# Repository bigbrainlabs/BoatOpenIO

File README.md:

# BoatOpenIO

**Universal Marine IO System – Open Source, modular, fully configurable**

> *"Plug in, configure, done."*

BoatOpenIO is an open hardware platform for sensor integration on boats. Each of the 16 sensor terminals can be freely assigned to any of the up to 16 input channels via software. Pluggable mini-boards handle signal conditioning — no soldering, no rewiring.

Part of the **[Logbook Without Posing](https://www.amazon.com/s?k=logbook+without+posing)** series – Volume 3.

---

## 📚 Support the project

This project is 100% open source and free. The complete story – every idea, mistake, detour and solution – is documented in the book series **"Logbook Without Posing"**.

If you find this project useful and want to support it: buying the books is the best way.

> *"Found this useful? Grab a book — or the whole series. You'll be supporting further development."*

**[👉 Logbook Without Posing on Amazon](https://amzn.to/4e5swN6)**

> **Note:** The ready-made board set is no longer sold on Tindie. Due to the new EU regulation on shipping abroad, the effort is no longer proportionate for me as a private individual. The Gerber files in this repo remain free to download.
>
> **The boards can be purchased directly from PCBWay** — I've set them up there as projects, so there's nothing to upload yourself: **[👉 BoatOpenIO projects on PCBWay](https://www.pcbway.com/project/member/?bmbno=0EDF2E80-7ABD-44)**

### 🏭 Boards sponsored by PCBWay

**[PCBWay](https://www.pcbway.com)** sponsors the board manufacturing for BoatOpenIO, the sensor gateway of this ecosystem — thank you!

**[👉 Order the boards directly: PCBWay project page](https://www.pcbway.com/project/member/?bmbno=0EDF2E80-7ABD-44)**

---

## ⚠️ Safety Warning

**Always verify which mini-board is plugged into which channel before applying power.**

Connecting 12V directly to a pull-up channel (instead of through a voltage divider) will destroy the MUX, all ADS1115 and the ESP32 through I2C chain reaction.

The input board includes protection circuitry (3.3V) on all 16 signal inputs — but correct mini-board assignment is still essential.

---

## Concept

Commercial marine IO systems cost hundreds of euros and are closed black boxes.

BoatOpenIO costs a fraction of that — and anyone can adapt, extend, and improve it.

```
Sensor → Mini-Board → JST 3-Pin → PCB → Zener Protection → MUX → ADS1115 → ESP32 → MQTT → BoatOS
```

---

## Who Is This For?

**If your boat was built before 2000, this project was built for you.**

Boats from that era came with **analog VDO sensors** — oil pressure, oil temperature, coolant temperature, tank level, RPM. These sensors are robust, time-tested, and still doing their job perfectly. The problem: no modern system speaks their language.

NMEA 2000 gateways that bridge analog signals to modern boat networks exist — but they cost **300–500€**, are closed proprietary boxes, and give you zero insight or control over what happens inside.

**BoatOpenIO is an open analog marine gateway.**

Plug in your existing VDO sensors. Get clean MQTT output. Forward to Signal K or BoatOS. Done — without replacing a single sensor, without rewiring, without a black box.

```
VDO sensor → BoatOpenIO → MQTT → Signal K / BoatOS → modern dashboard
```

> **Built for boats built before 2000 that will sail for another 20 years — and deserve a modern dashboard without a full refit.**

---

## Hardware – v2 PCB

Four separate boards, connected via IDC ribbon cables: **input board**, **main board**, **ESP32 adapter board**, and **VCC distributor**. Gerber files ready to order in `hardware/v2/*/gerber/`.

> 🛒 **Ordering the boards:** All four boards are set up as projects on PCBWay and can be purchased there directly: **[PCBWay project page](https://www.pcbway.com/project/member/?bmbno=0EDF2E80-7ABD-44)** — or upload the Gerbers to a PCB fab of your choice. Bare PCBs, components per the parts list below.

```
Input Board ──20-pin ribbon──> Main Board <──16-pin ribbon── ESP32 Adapter Board
                                    │
                               3-pin JST
                                    │
                               VCC Board
```

### Main Board Components

| Component | Description | Socketed |
|-----------|-------------|----------|
| ESP32-DEVKITC-32D-F (38-pin) | Microcontroller, WiFi, I2C, MUX control – on its own adapter board | ✅ |
| CD74HC4067 Breakout | 16:1 analog multiplexer | ✅ |
| ADS1115 Breakout (1×) | 16-bit ADC | ✅ |
| MPU6050 Breakout (GY-521) | 6-DOF IMU, tilt/impact detection | ✅ |
| AMS1117-3.3 Breakout | 5V → 3.3V regulator | ✅ |

**Everything socketed** — no component soldered directly. Faulty ESP32? Swap the adapter board. Done.

The ESP32 sits on its own dedicated adapter board. The first adapter board is designed for the 38-pin ESP32 DevKitC-32D — swappable and ready for future ESP32 variants.

### Protection Circuit (Input Board)

Every one of the 16 signal inputs has a hardware protection circuit, directly on the input board:

```
Sensor → Screw terminal → R_Pack08 (resistor network) → SP0503BAHTG (Zener array, 3.3V) → MUX signal
```

2× Bourns 4116R-1-102LF (R_Pack08, DIL-16, isolated) + 6× SP0503BAHTG (SOT-143, 3 channels each).

> ⚠️ **Pull-up voltage is 3.3V** — the ADS1115 VDD is at 3.3V; higher voltages on the inputs risk component damage.

#### Running without the protection circuit (not recommended)

If the Bourns or Zener components are unavailable and you want to get the board running first, the resistor networks can be bypassed — but understand what you are giving up.

**How to bypass the Bourns 4116R-1-102LF:**  
The DIL-16 package contains 8 isolated resistors. Each resistor connects a pin on the left row to the opposing pin on the right row:

```
Pin 1  ──[R]──  Pin 16
Pin 2  ──[R]──  Pin 15
Pin 3  ──[R]──  Pin 14
  ...             ...
Pin 8  ──[R]──  Pin 9
```

To bypass: solder a short jumper wire across each pair (8 bridges per chip, 16 total for both R_Pack08). The signal then passes through without series resistance. The SP0503BAHTG Zener pads can simply be left empty.

> 🔴 **Without this protection, all 16 inputs are exposed.** A wrong mini-board, a wiring mistake, or any brief overvoltage can destroy the MUX, ADS1115, and ESP32 in a chain reaction — all three at once. Only bypass for bench tests with known, clean signals. Fit the real parts before installing on the boat.

### Input Board – Connectors

```
16× screw terminal 5.08mm   → raw sensor signal
20-pin IDC header            → connection to main board (SIG1–16 + GND)
```

### VCC Board – Connectors

The VCC board distributes power to the mini-boards via JST connectors. It connects to the main board via a 3-pin JST cable (5V, 3.3V, GND).

```
7× JST 2-pin (3.3V)         → VCC rail for passive/ESP01 mini-boards
3× JST 2-pin (5V)           → VCC rail for Arduino Nano mini-boards
3-pin JST                   → connection to main board (5V · 3.3V · GND)
```

### I2C Address

Only 1× ADS1115 fitted (the MUX routes all 16 channels onto a single signal line) → fixed address **0x48**.

### GPIO Assignment (ESP32, via 16-pin main board ↔ adapter board connector)

| GPIO | Function |
|------|----------|
| GPIO21 | I2C SDA |
| GPIO22 | I2C SCL |
| GPIO14 | MUX S0 |
| GPIO27 | MUX S1 |
| GPIO26 | MUX S2 |
| GPIO25 | MUX S3 |
| GPIO4 / 5 / 13 / 16 / 17 / 18 / 19 / 23 | OUT1–OUT8 (prepared for output channels) |

### Output Channels (prepared)

The main board already has a 10-pin header prepared for 8 signal output channels (+5V/GND) — e.g. for heaters, pumps, horns via relay or MOSFET mini-boards. Works on the same plug-in principle as the inputs.

### Compatible ESP32 Modules (first adapter board)

The footprint fits all modules in the 38-pin DevKitC layout: **ESP32-WROOM-32 / -32D / -32E / -32U / -32UE**, as well as **ESP32-SOLO-1**.

> ⚠️ **ESP32-WROVER is NOT compatible** — GPIO16/17 are internally reserved for PSRAM on WROVER and therefore blocked for output channels.

---

## Mini-Boards (pluggable)

| Type | Code | Use case |
|------|------|----------|
| Voltage divider | VT | 12V VDO sensors → 3.3V |
| Pull-down | PD | Digital sensors, switches |
| Pull-up | PU | Open-collector outputs |
| Schmitt trigger | ST | Magnetic pickup sensors, 50Hz generators |
| Pulse board | ISP | RPM, flow (Arduino Nano / ESP01) |
| Optocoupler | OPT | Galvanic isolation (W-terminal RPM) |
| Direct / jumper | DIR | 3.3V signals directly |
| GND collector | GND | Multiple sensor ground loops → single reference |

### MotorCombo — everything on one board

The **MotorCombo** taps the most common engine sensors directly, so you don't have to plug in six separate mini-boards:

| Channel | Conditioning |
|---------|--------------|
| Battery 1 + 2 | Voltage divider |
| Oil pressure | Pull-up |
| Temperature | Pull-up |
| Tank | Pull-up |
| RPM | Optocoupler + ESP-01 |

**[MotorCombo THT](hardware/mini-boards/MotorCombo_THT/README.md)** — through-hole, hand-solderable. Gerbers and documentation are in the repo. Resistor values are deliberately left open so everyone can fit what matches their own VDO senders — which is also why there is no pre-assembled SMD variant: with the values depending on the senders, a fixed pre-populated board makes no sense.

**Design and submit your own mini-boards** — pull requests welcome!

---

## Multiplexer Logic

The CD74HC4067 routes one of 16 inputs onto the shared ADS pin A0 via a 4-bit address (S3–S0). Address and chip input follow the datasheet: `0000 → C0` … `1111 → C15`.

> **Rev.1 note — channels are mirrored in software.** On the Rev.1 board the channel wiring is reversed (terminal 1 sits on the input that address `1111` selects, terminal 16 on `0000`). The firmware compensates in software (`MUX_MIRROR`): terminal *N* → address `16 − N`. The terminal numbering you see is therefore correct. A later board revision straightens the wiring, then the mirror is switched off (`MUX_MIRROR 0`).

| Terminal | Address S3 S2 S1 S0 | CD74HC4067 input |
|----------|---------------------|------------------|
| 1        | `1111`              | C15              |
| 2        | `1110`              | C14              |
| …        | …                   | …                |
| 16       | `0000`              | C0               |

---

## Software Configuration

```json
{
  "kanaele": [
    {"klemme": 1, "sensor": "battery1",     "einheit": "V",   "faktor": 4.7, "offset": 0, "aktiv": true,  "topic": ""},
    {"klemme": 2, "sensor": "oil_temp",     "einheit": "°C",  "faktor": 1.0, "offset": 0, "aktiv": true,  "topic": "vessels/self/propulsion/engine/oilTemperature"},
    {"klemme": 3, "sensor": "oil_pressure", "einheit": "bar", "faktor": 1.0, "offset": 0, "aktiv": true,  "topic": "vessels/self/propulsion/engine/oilPressure"},
    {"klemme": 4, "sensor": "tank",         "einheit": "%",   "faktor": 1.0, "offset": 0, "aktiv": true,  "topic": ""},
    {"klemme": 5, "sensor": "rpm",          "einheit": "rpm", "faktor": 1.0, "offset": 0, "aktiv": false, "topic": ""}
  ]
}
```

> All 16 channels are routed via the MUX (CD74HC4067) to a single ADS1115 @ 0x48 on pin A0. No `ads` or `pin` fields needed — the channel number (`klemme`) maps directly to the MUX select lines.
>
> **`topic`** — optional. If empty (`""`), the firmware publishes to `boat/io/<sensor>` (default). Set a custom topic for Signal K compatibility or any other MQTT schema. The "SK" button in the web UI auto-fills the correct Signal K path for common sensor names.

---

## MQTT Topics

```
boat/io/battery1          → 12.43
boat/io/oil_temp          → 87
boat/io/oil_pressure      → 3.2
boat/io/tank              → 48
boat/io/rpm               → 1450
boat/io/pitch             → 1.2        (configurable)
boat/io/roll              → -0.5       (configurable)
boat/alarm/impact_g       → 2.40       (impact base configurable)
boat/alarm/impact_severity → KRITISCH  (LEICHT / MITTEL / STARK / KRITISCH)
boat/alarm/impact_active  → true
boatopenio/status         → online
```

> **Channel topics** are set per channel (`topic` field / web UI). **Pitch, roll and the impact base topic** are editable under **WiFi & MQTT** in the web UI (defaults `boat/io/pitch`, `boat/io/roll`, `boat/alarm/impact`; the impact base gets `_g` / `_severity` / `_active` appended). In test mode the impact alarms are redirected to `boat/test/alarm/impact_*` so demo impacts never trigger real dashboards.

---

## Firmware Features

| Feature | Description |
|---------|-------------|
| Web UI | Configuration at `192.168.4.1`, bilingual DE/EN |
| WiFiManager | AP on first start for WiFi setup |
| MQTT | Publish all sensor values, LWT, auth support |
| OTA | Over-the-air firmware updates |
| mDNS | Reachable as `boatopenio.local` |
| Impact Detection | MPU6050 G-force monitoring with severity levels |
| Watchdog | Automatic restart on firmware hang |
| LittleFS | Persistent configuration storage |

---

## Supported Sensors

| Sensor | Type | Mini-Board |
|--------|------|------------|
| VDO temperature (NTC) | Resistance | VT |
| VDO oil pressure | Linear resistance | VT |
| VDO tank sender | Potentiometer | VT |
| Battery voltage 12V | Voltage divider | VT (10k/2.2k) |
| RPM (W-terminal) | Pulse/AC | OPT + ISP |
| RPM (magnetic pickup) | AC signal | ST + ISP |
| Fuel flow | Pulse | ISP |
| Bilge sensor | Digital | PD |
| Door/hatch contact | Digital | PD |
| DS18B20 temperature | Digital 1-Wire | custom board |

---

## Bill of Materials – PCB Kit

**[👉 Complete parts list on Amazon](https://www.amazon.de/hz/wishlist/ls/2ZLKK0GZJ5RZE?&linkCode=ll2&tag=bigbrainlab08-21&linkId=caccb90fad5cfe3e58063e29c1bc7dd4&ref_=as_li_ss_tl)**

> **Note:** Items 7, 8, 13, and 14 are from the same set — one purchase covers all. Same applies to 12 and 15.

| # | Component | Notes | Source |  |
|---|-----------|-------|--------|---|
| 1 | ESP32 DevKitC-32D (38-pin) | Main controller | [Amazon](https://amzn.to/441f1bl) |  |
| 2 | CD74HC4067 Breakout | 16:1 MUX | [Amazon](https://amzn.to/4vPmaHH) |  |
| 3 | ADS1115 Breakout (1×) | 16-bit ADC | [Amazon](https://amzn.to/4gg8mRQ) |  |
| 4 | MPU6050 Breakout (GY-521) | IMU | [Amazon](https://amzn.to/3S3gGKJ) |  |
| 5 | AMS1117-3.3 Breakout | Voltage regulator | [Amazon](https://amzn.to/4gfqqeL) |  |
| 6 | Female header assortment | Sockets for all breakouts | [Amazon](https://amzn.to/3S1rXLD) |  |
| 7 | Pin header 2×10 (20-pin) | Main board ↔ input board | [Amazon](https://amzn.to/4f2awU6) |  |
| 8 | Pin header 2×08 (16-pin) | Main board ↔ ESP32 adapter board | [Amazon](https://amzn.to/4f2awU6) |  |
| 9 | Screw terminals 5.08mm | 16× sensor inputs | [Amazon](https://amzn.to/4e6bJcN) |  |
| 10 | Bourns 4116R-1-102LF (2×) | Resistor network DIL-16 | [Conrad](https://www.conrad.de/de/p/bourns-4116r-1-102lf-4116r-1-102lf-widerstandsnetzwerk-1-k-radial-bedrahtet-dip-16-0-25-w-1-st-1055156.html) | [Amazon](https://amzn.to/3SuSZeD) |
| 11 | SP0503BAHTG (6×) | Zener array SOT-143 | [Amazon](https://amzn.to/4aippiv) |  |
| 12 | JST 2-pin connector | VCC rails | [Amazon](https://amzn.to/43y2Suh) |  |
| 13 | Pin header 2×10 (20-pin) | Input board side | [Amazon](https://amzn.to/4f2awU6) |  |
| 14 | Pin header 2×08 (16-pin) | ESP32 adapter board side | [Amazon](https://amzn.to/4f2awU6) |  |
| 15 | JST 2-pin connector (10×) | VCC distribution | [Amazon](https://amzn.to/43y2Suh) |  |
| 16 | Ribbon cable + IDC 20-pin | Main board ↔ input board | [Amazon](https://amzn.to/4w6858M) |  |
| 17 | Ribbon cable + IDC 16-pin | Main board ↔ ESP32 adapter board | [Amazon](https://amzn.to/3SuZ3DQ) |  |
| 18 | Pin socket 2×05 (10-pin) | SIG-OUT prep on main board | — |  |
| 19 | JST 3-pin connector | VCC board ↔ main board | [Amazon](https://amzn.to/4ush82N) |  |
| 20 | PCB set (4 boards) | Order the Gerbers in `hardware/v2/` yourself | [PCBWay](https://www.pcbway.com/project/member/?bmbno=0EDF2E80-7ABD-44) |  |

> Amazon: faster delivery. AliExpress links to follow.
>
> **Item 10 comes from Conrad**, not Amazon: the same Bourns part is around €1.30 there versus roughly €10. For the 2 pieces needed that saves nearly €18. The Amazon link beside it is just the fallback source.
>
> Item 20 is the bare boards only. Items 1–19 are the components you still need.

---

## Directory Structure

```
BoatOpenIO/
├── README.md                          ← English (this file)
├── README_de.md                       ← German version
├── LICENSE                            ← GPL-3.0
├── boatopenio_final_architektur.svg   ← system architecture diagram
├── firmware_src/
│   ├── firmware_src.ino               ← main firmware
│   ├── webui.h                        ← web UI & captive portal
│   └── data/
│       └── config.json                ← default channel config
├── hardware/
│   ├── boatopenio-gehaeuse-draufsicht.svg  ← housing top-view
│   ├── mini-boards/                   ← mini-board designs
│   └── v2/                            ← KiCad PCB project (4 boards)
│       ├── main-board/
│       │   └── gerber/main-board.zip
│       ├── input-board/
│       │   └── gerber/input-board.zip
│       ├── esp32-adapter-board/
│       │   └── gerber/esp32-adapter-board.zip
│       └── vcc-board/
│           └── gerber/vcc-board.zip
├── images/                            ← build photos
└── docs/
    ├── setup.md              / setup_de.md          ← commissioning guide
    ├── configuration.md      / configuration_de.md  ← config reference
    └── backend.md            / backend_de.md        ← firmware & backend reference
```

---

## Roadmap

What's done, what's planned, what's on the backlog — see [ROADMAP.md](ROADMAP.md).

---

## Integration with BoatOS

BoatOpenIO sends all values via MQTT. BoatOS auto-discovers all topics and displays them in the dashboard. No manual configuration needed.

**➡️ [github.com/bigbrainlabs/BoatOS](https://github.com/bigbrainlabs/BoatOS)**

---

## License

**GNU General Public License v3.0 (GPL-3.0)**

Free to use, modify, distribute — derivative works must also be GPL-3.0. See [LICENSE](LICENSE).

**Exception:** the community enclosure designs in `hardware/enclosures/` are licensed **CC BY-SA 4.0** — the better fit for CAD work. Submitting a design means licensing it that way; see the [enclosure README](hardware/enclosures/README.md).

---

## Part of the Series

**Logbook Without Posing** — authentic DIY projects around boating.

> *"Build it yourself and you know what's in it — and what it cost."*

📖 [Book series on Amazon](https://amzn.to/4e5swN6) · 🔧 [BoatOS](https://github.com/bigbrainlabs/BoatOS) · ⚡ [BoatOpenIO](https://github.com/bigbrainlabs/BoatOpenIO)

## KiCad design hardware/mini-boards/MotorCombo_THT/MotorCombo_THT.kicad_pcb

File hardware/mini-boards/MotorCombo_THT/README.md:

# MotorCombo THT — Combo Mini-Board for Engine Sensors

> 🚧 **Prototype stage.** This board (Rev.1) has not been fully validated yet. Five of the six channels are tested, the RPM channel is not (see below). Resistor values, mounting holes and layout may still change in future revisions. Build at your own risk, and ideally with feedback.

Through-hole (THT) variant of the MotorCombo board. Combines the six typical engine room signals onto a single board instead of plugging in six separate mini-boards.

Every part is through-hole — hand-solderable, no SMD equipment needed.

---

## Channels

| Channel | Connector | Signal conditioning | Typical sensor |
|---------|-----------|---------------------|----------------|
| Battery 1 | `Batt1` | Voltage divider (R1 / R2) | 12 V house voltage |
| Battery 2 | `Batt2` | Voltage divider (R3 / R4) | Second battery bank |
| Tank | `Tank1` | Pull-up to 3.3 V (R5) | VDO tank sender, resistive |
| Temperature | `Temp1` | Pull-up to 3.3 V (R6) | VDO temperature sender, resistive |
| Oil pressure | `Oil1` | Pull-up to 3.3 V (R7) | VDO pressure sender, resistive |
| RPM | `RPM1` | Optocoupler PC817 + ESP-01 | Alternator W terminal, pulse pickup |

Every channel has a 100 nF capacitor for signal smoothing (C1–C6).

> Channels 1–5 (`Batt1`, `Batt2`, `Tank1`, `Temp1`, `Oil1`) are **not hardwired** to one mode — two solder jumpers per channel select pull-up or voltage-divider. See [Channel Mode — Jumpers](#channel-mode--jumpers-channels-15). The table shows the typical default for each sensor.

---

## Signal Path

Per the netlist, the JST 3-pin connectors are wired as **input / GND / output**: the raw signal arrives on pin 1, the conditioned signal returns on pin 3.

```
Pin 1 (raw) → conditioning → Pin 3 (conditioned)
Pin 2 = GND
```

**Voltage divider (Batt1, Batt2)**
```
Pin 1 ──[R1]──┬── Pin 3
              ├── C1 ── GND
              └──[R2]── GND
```

**Pull-up (tank, temperature, oil)**
```
3.3 V ──[R5]──┬── Pin 1 = Pin 3
              └── C3 ── GND
```
Pin 1 and pin 3 are tied together — the resistive sender forms the divider together with the pull-up resistor.

**RPM (RPM1)**
```
Pin 1 ──[R8]── PC817 LED ── GND
               PC817 transistor ── GPIO0 (ESP-01), pull-up R9
               GPIO2 ──[R10]──┬── Pin 3
                              └── C6 ── GND
```
The optocoupler isolates the pulse input galvanically. The ESP-01 counts the pulses and outputs an RPM-proportional value on pin 3.

---

## Channel Mode — Jumpers (channels 1–5)

Channels 1–5 (`Batt1`, `Batt2`, `Tank1`, `Temp1`, `Oil1`) are **not hardwired to one mode**. Two solder jumpers **JP1** and **JP2** plus the channel's divider resistor **R2** select **pull-up** (resistive VDO senders) or **voltage-divider** (active voltage inputs) — per channel.

**JP1 (3 pads):**
- **P1 = 3.3 V** (pull-up)
- **P3 = SIG-IN** (voltage divider)
- **P2 = common** (centre pad)

| | Pull-up mode | Voltage-divider mode |
|---|---|---|
| **JP1** | bridge **P2–P3** | bridge **P2–P1** |
| **JP2** | **bridged** | **open** |
| **R2** (channel divider resistor) | **fit a bridge** (0 Ω) | **fit** |

- **Pull-up:** JP1 P2–P3 closed, JP2 closed, R2 position populated with a **bridge** (a 0 Ω resistor in the same footprint, or a wire link) — the pull-up is active and SIG-OUT is passed through. **Important:** do not leave R2 open here. The board has no separate direct GND connection, so the R2 position provides the ground for the smoothing capacitor; left open, the ceramic cap would sit in series in the signal path instead of to ground.
- **Voltage divider:** JP1 P2–P1 closed, JP2 open, R2 fitted — the divider is formed.

Channel 6 (`RPM1`) is the optocoupler + ESP-01 path and has no mode jumper.

---

## Connectors

| Designator | Type | Function |
|------------|------|----------|
| `Batt1`, `Batt2`, `Tank1`, `Temp1`, `Oil1`, `RPM1` | JST PH 3-pin, 2.0 mm | Channels to the main board |
| `J7` | JST PH 2-pin, 2.0 mm | 3.3 V / GND supply from the VCC board |
| `GND_Collector1` | Screw terminal 5-way, 5.08 mm | Common point for sensor grounds |

---

## Board

| | |
|---|---|
| Revision | Rev.1 |
| Dimensions | 75 × 55 mm |
| Layers | 2 |
| Assembly | through-hole throughout |
| Mounting | 4 holes, one per corner |
| Gerbers | [`gerber/`](gerber/) — ready to order, ZIP included |

> 🏭 **Order ready-made:** the boards are sponsored by [PCBWay](https://www.pcbway.com) and shared in the [PCBWay project](https://www.pcbway.com/project/member/?bmbno=0EDF2E80-7ABD-44) — order directly, no Gerber upload needed.
>
> 

---

## Bill of Materials

| Item | Part | Qty | Package |
|------|------|-----|---------|
| 1 | Resistor, axial | 10 | DIN0204, 7.62 mm pitch |
| 2 | Capacitor 100 nF, ceramic | 6 | disc D5 mm, 5.00 mm pitch |
| 3 | PC817 optocoupler | 1 | DIP-4 |
| 4 | ESP-01 (ESP8266) | 1 | ESP-01 module, 2×4 socket |
| 5 | JST PH header 3-pin, vertical | 6 | B3B-PH-K |
| 6 | JST PH header 2-pin, vertical | 1 | B2B-PH-K |
| 7 | Screw terminal 5-way | 1 | Phoenix MKDS-3/5-5.08 |

---

## Resistor Values

**Values R1–R10 are deliberately left open in the schematic.** VDO senders differ in resistance range depending on year and manufacturer — a value that works cleanly on one engine can cause distorted readings on the next. Rather than prescribing one size, everyone fits what matches their own senders.

The following values have proven themselves in practice and are a good starting point:

| Channel | Resistors | Recommended | Alternative |
|---------|-----------|-------------|-------------|
| Battery 1 | R1 / R2 | 10 kΩ / 2.2 kΩ | 100 kΩ / 22 kΩ |
| Battery 2 | R3 / R4 | 10 kΩ / 2.2 kΩ | 100 kΩ / 22 kΩ |
| Tank | R5 | 10 kΩ | adjust to your sender |
| Temperature | R6 | 10 kΩ | adjust to your sender |
| Oil pressure | R7 | 10 kΩ | adjust to your sender |

**Voltage dividers.** 10 kΩ / 2.2 kΩ is tested and works. The divider ratio is 2.2 / (10 + 2.2) = 0.180, so 12 V becomes roughly 2.16 V. As a factor in the channel configuration that works out to about **5.55**, and with a 3.3 V input limit the upper end lands at roughly 18 V. The 100 kΩ / 22 kΩ variant has the same ratio but loads the battery ten times less — at the cost of being more susceptible to interference.

**Pull-ups.** 10 kΩ has shown itself to be a good compromise in testing. If a sender uses a different resistance range, the pull-up should be adjusted along with it — best measured on the installed sender, choosing a value that makes good use of the measuring range.

**Optocoupler.** R8 sets the PC817 LED current, R9 is the pull-up at the ESP-01. This combination has not yet been proven in practice (see below).

---

## ESP-01 Notes

The ESP-01 is **socketed** — it needs a dedicated USB adapter for flashing anyway, so it is taken out of the board for programming. That is why `RST`, `URXD` and `UTXD` are left unconnected.

> 🚧 **The RPM channel via PC817 and ESP-01 has not been tested in practice yet.** The other five channels are proven.

Worth keeping in mind during assembly: on the ESP8266, `GPIO0` and `GPIO2` double as boot-mode straps, and both are wired here.

- **GPIO0** is tied to the optocoupler transistor. If a pulse happens to be present at power-on, the optocoupler pulls GPIO0 low and the ESP-01 boots into flash mode instead of running the firmware — quite possible with the engine running.
- **GPIO2** drives the output through R10. C6 is discharged at power-on — depending on the values chosen for R10 and C6, this may hold GPIO2 low for too long during boot.

Both depend on the values of R8, R9, R10 and C6, and can be settled together when the RPM channel is trialled.

> 💡 **Tip: use an ESP-01S instead of an ESP-01.** The newer ESP-01S variant already has a pull-up fitted on GPIO0. This mitigates the boot-mode issue above, since GPIO0 is safely held high at idle. The ESP-01S is pin-compatible and fits the same socket.

---

## Safety

> ⚠️ **Verify which channel sits on which terminal before applying power.**
>
> The battery channels are designed for 12 V through voltage dividers. If 12 V accidentally reaches one of the pull-up channels (tank, temperature, oil), it will destroy the MUX, ADS1115 and ESP32 through an I2C chain reaction. See the safety warning in the [main README](../../../README.md).

---

## License

GPL-3.0, same as the rest of the repo. See [LICENSE](../../../LICENSE).

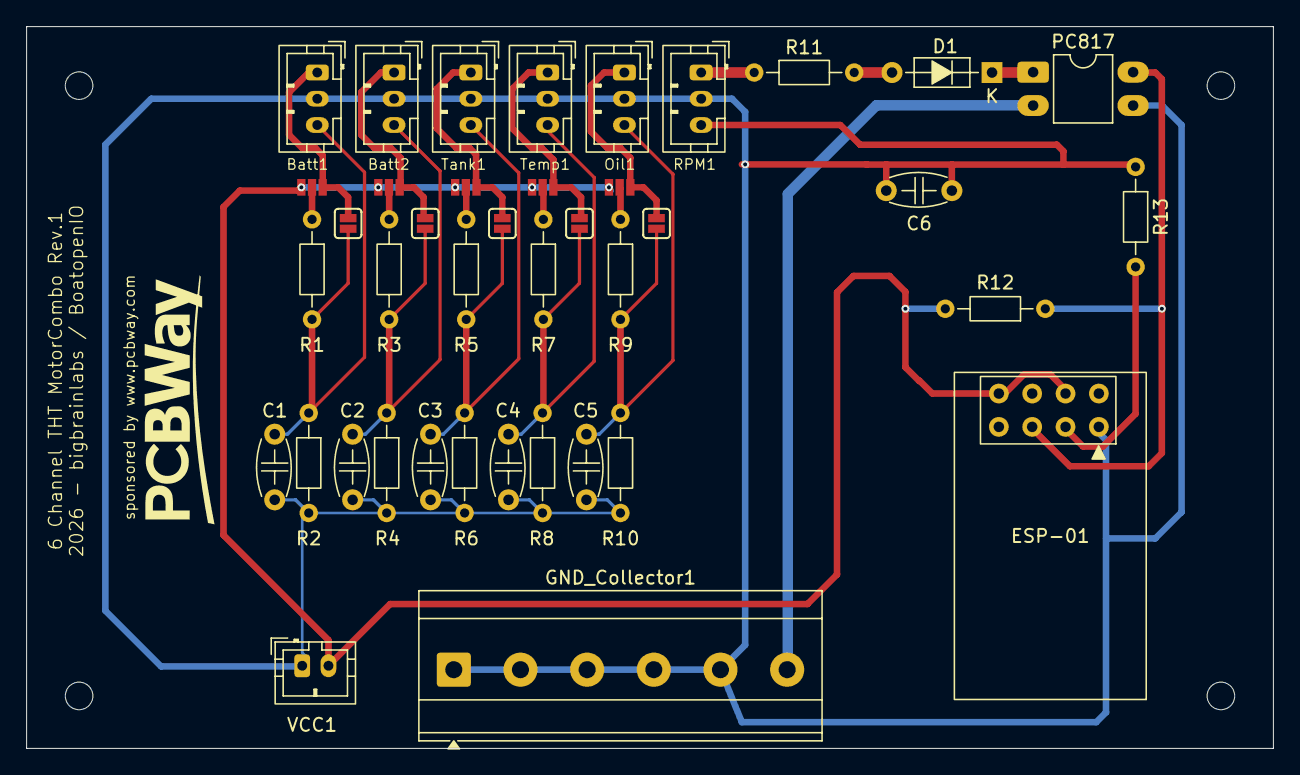
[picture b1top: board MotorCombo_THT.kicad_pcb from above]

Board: 2 copper layers, 95.0 x 55.0 mm, 40 parts (0 on the bottom side), 23 nets.

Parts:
Batt1, Batt2: JST_2mm_3; JST_PH_B3B-PH-K_1x03_P2.00mm_Vertical
C1, C2, C3, C4, C5: 100nF_Ceramic; C_Disc_D5.0mm_W2.5mm_P5.00mm
C6: 100nF; C_Disc_D5.0mm_W2.5mm_P5.00mm
D1: 1N4148; D_DO-35_SOD27_P7.62mm_Horizontal
ESP-01: ESP-01v090; ESP-01
GND_Collector1: Screw_Terminal_01x05; TerminalBlock_Phoenix_MKDS-3-6-5.08_1x06_P5.08mm_Horizontal
JP1, JP3, JP5, JP7, JP9: Jumper_3_Open; Jumper_3_NO_NoSilk
JP2, JP4, JP6, JP8, JP10: Jumper_2_Open; Jumper_2_NO
Oil1: JST_2mm_3; JST_PH_B3B-PH-K_1x03_P2.00mm_Vertical
PC817: PC817; DIP-4_W7.62mm_LongPads
R1, R2, R3, R4, R5, R6, R7, R8, R9, R10: R; R_Axial_DIN0204_L3.6mm_D1.6mm_P7.62mm_Horizontal
R11: 1k; R_Axial_DIN0204_L3.6mm_D1.6mm_P7.62mm_Horizontal
R12, R13: 10k; R_Axial_DIN0204_L3.6mm_D1.6mm_P7.62mm_Horizontal
RPM1: JST_2mm_3; JST_PH_B3B-PH-K_1x03_P2.00mm_Vertical
Tank1: JST_2mm_3; JST_PH_B3B-PH-K_1x03_P2.00mm_Vertical
Temp1: JST_2mm_3; JST_PH_B3B-PH-K_1x03_P2.00mm_Vertical
VCC1: Conn_01x02; JST_PH_B2B-PH-K_1x02_P2.00mm_Vertical

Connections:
GND: Batt1.2, Batt2.2, C1.1, C2.1, C3.1, C4.1, C5.1, C6.1, C6.2, ESP-01.1 (GND), GND_Collector1.1, GND_Collector1.2, GND_Collector1.3, GND_Collector1.4, GND_Collector1.5, Oil1.2, PC817.3, R2.2, R4.2, R6.2, R8.2, R10.2, R13.1, RPM1.2, RPM1.3, Tank1.2, Temp1.2, VCC1.1
unnamed: D1.2 (A), R11.2
unnamed: D1.1 (K), PC817.1
unnamed: ESP-01.7 (CH_PD), ESP-01.8 (VCC), JP1.1 (A), JP3.1 (A), JP5.1 (A), JP7.1 (A), JP9.1 (A), R12.2, VCC1.2
unnamed: ESP-01.2 (GPIO0), PC817.4, R12.1
unnamed: ESP-01.5 (GPIO2), R13.2
unnamed: GND_Collector1.6, PC817.2
unnamed: Batt1.1, JP1.3 (B), JP2.2 (B)
unnamed: JP1.2 (C), R1.1
unnamed: Batt1.3, C1.2, JP2.1 (A), R1.2, R2.1
unnamed: Batt2.1, JP3.3 (B), JP4.2 (B)
unnamed: JP3.2 (C), R3.1
unnamed: Batt2.3, C2.2, JP4.1 (A), R3.2, R4.1
unnamed: JP5.3 (B), JP6.2 (B), Tank1.1
unnamed: JP5.2 (C), R5.1
unnamed: C3.2, JP6.1 (A), R5.2, R6.1, Tank1.3
unnamed: JP7.3 (B), JP8.2 (B), Temp1.1
unnamed: JP7.2 (C), R7.1
unnamed: C4.2, JP8.1 (A), R7.2, R8.1, Temp1.3
unnamed: JP9.2 (C), R9.1
unnamed: C5.2, JP10.1 (A), Oil1.3, R9.2, R10.1
unnamed: JP9.3 (B), JP10.2 (B), Oil1.1
unnamed: R11.1, RPM1.1

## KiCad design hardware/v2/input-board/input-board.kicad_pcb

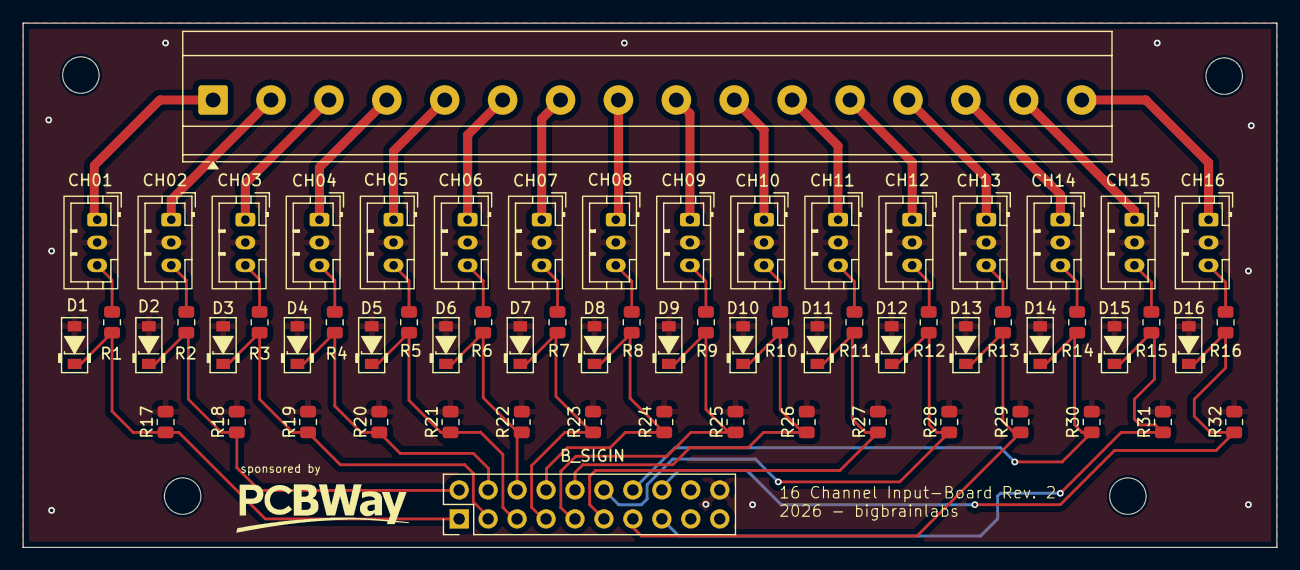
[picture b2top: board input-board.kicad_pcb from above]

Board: 2 copper layers, 110.0 x 46.0 mm, 70 parts (0 on the bottom side), 49 nets.

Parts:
B11, B12, B13, B14: MountingHole_3.2mm_M3
B_SIGIN: Conn_02x10_Odd_Even; PinHeader_2x10_P2.54mm_Vertical
CH01, CH02, CH03, CH04, CH05, CH06, CH07, CH08, CH09, CH10, CH11, CH12, CH13, CH14, CH15, CH16: Conn_01x03_Pin; JST_PH_B3B-PH-K_1x03_P2.00mm_Vertical
D1, D2, D3, D4, D5, D6, D7, D8, D9, D10, D11, D12, D13, D14, D15, D16: D_Zener; D_SOD-123_Zener
J27: Screw_Terminal_01x16; TerminalBlock_Phoenix_MKDS-3-16-5.08_1x16_P5.08mm_Horizontal
R1, R2, R3, R4, R5, R6, R7, R8, R9, R10, R11, R12, R13, R14, R15, R16: 1k; R_0805_2012Metric
R17, R18, R19, R20, R21, R22, R23, R24, R25, R26, R27, R28, R29, R30, R31, R32: 1M; R_0805_2012Metric

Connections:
GND: B_SIGIN.20, CH01.2, CH02.2, CH03.2, CH04.2, CH05.2, CH06.2, CH07.2, CH08.2, CH09.2, CH10.2, CH11.2, CH12.2, CH13.2, CH14.2, CH15.2, CH16.2, D1.2 (A), D2.2 (A), D3.2 (A), D4.2 (A), D5.2 (A), D6.2 (A), D7.2 (A), D8.2 (A), D9.2 (A), D10.2 (A), D11.2 (A), D12.2 (A), D13.2 (A), D14.2 (A), D15.2 (A), D16.2 (A), R17.2, R18.2, R19.2, R20.2, R21.2, R22.2, R23.2, R24.2, R25.2, R26.2, R27.2, R28.2, R29.2, R30.2, R31.2, R32.2
unnamed: B_SIGIN.1, D1.1 (K), R1.1, R17.1
unnamed: B_SIGIN.2, D2.1 (K), R2.1, R18.1
unnamed: B_SIGIN.3, D3.1 (K), R3.1, R19.1
unnamed: B_SIGIN.4, D4.1 (K), R4.1, R20.1
unnamed: B_SIGIN.5, D5.1 (K), R5.1, R21.1
unnamed: B_SIGIN.6, D6.1 (K), R6.1, R22.1
unnamed: B_SIGIN.7, D7.1 (K), R7.1, R23.1
unnamed: B_SIGIN.8, D8.1 (K), R8.1, R24.1
unnamed: B_SIGIN.9, D9.1 (K), R9.1, R25.1
unnamed: B_SIGIN.10, D10.1 (K), R10.1, R26.1
unnamed: B_SIGIN.11, D11.1 (K), R11.1, R27.1
unnamed: B_SIGIN.12, D12.1 (K), R12.1, R28.1
unnamed: B_SIGIN.13, D13.1 (K), R13.1, R29.1
unnamed: B_SIGIN.14, D14.1 (K), R14.1, R30.1
unnamed: B_SIGIN.15, D15.1 (K), R15.1, R31.1
unnamed: B_SIGIN.16, D16.1 (K), R16.1, R32.1
unnamed: CH01.1, J27.1
unnamed: CH01.3, R1.2
unnamed: CH02.1, J27.2
unnamed: CH02.3, R2.2
unnamed: CH03.3, R3.2
unnamed: CH04.3, R4.2
unnamed: CH05.3, R5.2
unnamed: CH06.3, R6.2
unnamed: CH07.3, R7.2
unnamed: CH08.3, R8.2
unnamed: CH09.3, R9.2
unnamed: CH10.1, J27.10
unnamed: CH10.3, R10.2
unnamed: CH11.1, J27.11
unnamed: CH11.3, R11.2
unnamed: CH12.1, J27.12
unnamed: CH12.3, R12.2
unnamed: CH13.1, J27.13
unnamed: CH13.3, R13.2
unnamed: CH14.1, J27.14
unnamed: CH14.3, R14.2
unnamed: CH15.1, J27.15
unnamed: CH15.3, R15.2
unnamed: CH16.1, J27.16
unnamed: CH16.3, R16.2
unnamed: CH03.1, J27.3
unnamed: CH04.1, J27.4
unnamed: CH05.1, J27.5
unnamed: CH06.1, J27.6
unnamed: CH07.1, J27.7
unnamed: CH08.1, J27.8
unnamed: CH09.1, J27.9

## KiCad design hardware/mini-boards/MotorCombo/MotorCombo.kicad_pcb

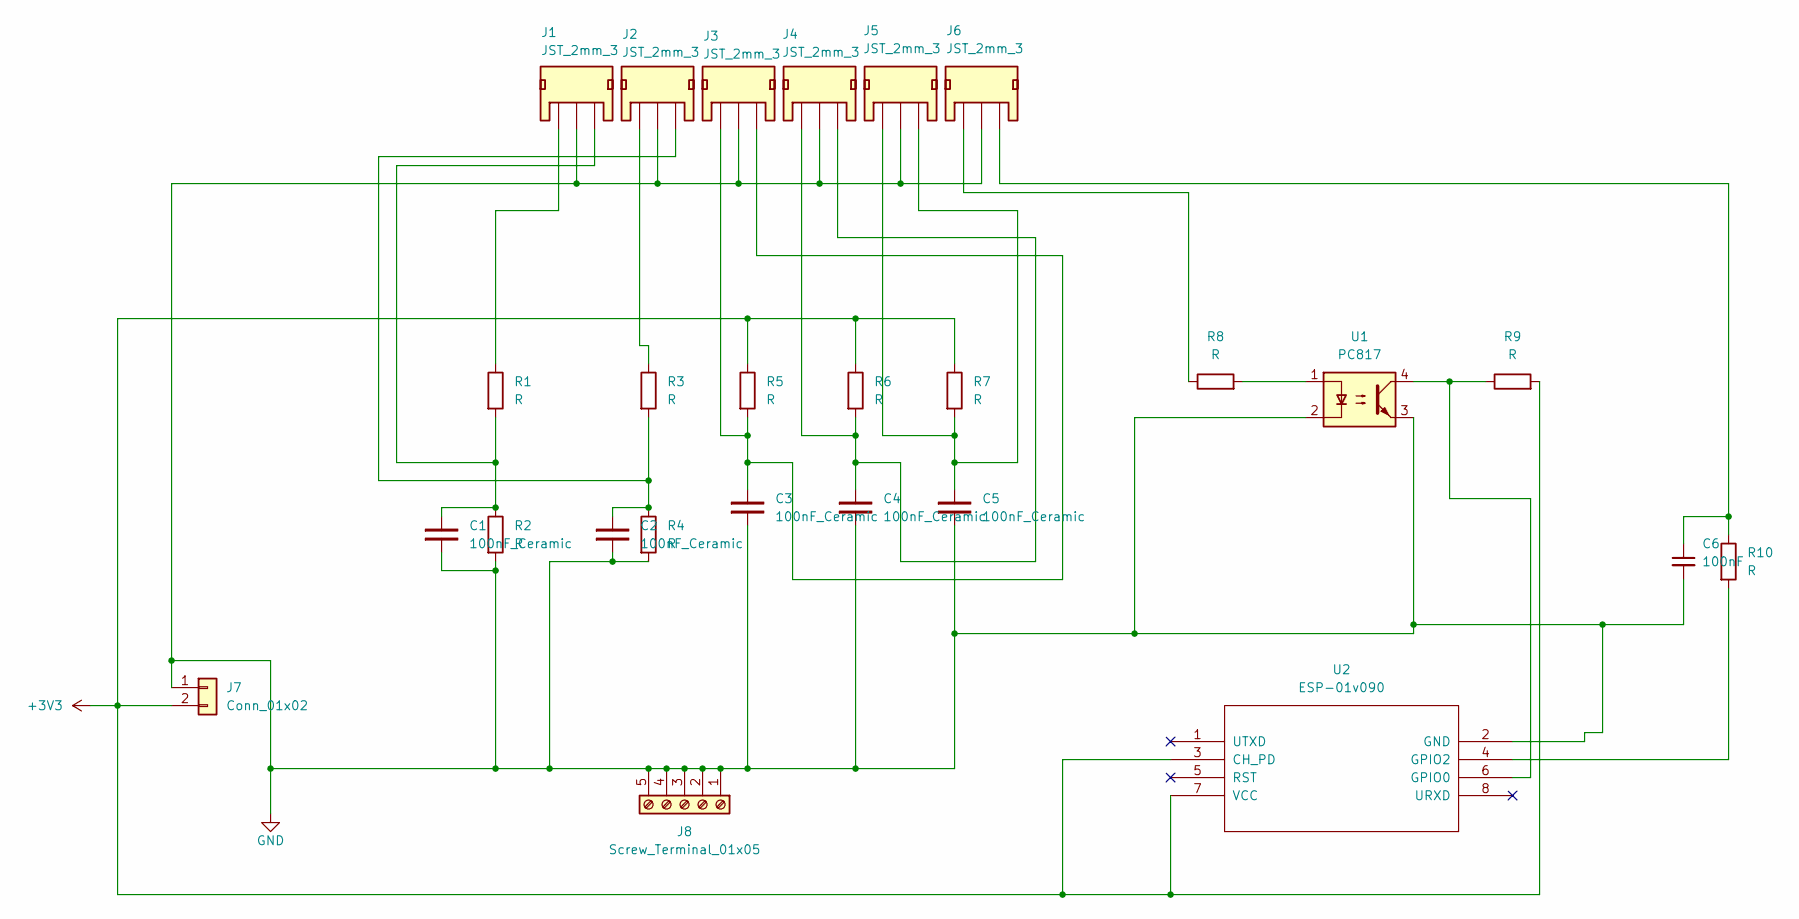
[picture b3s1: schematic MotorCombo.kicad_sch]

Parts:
C1, C2, C3, C4, C5: 100nF_Ceramic; R_0805_2012Metric_Pad1.20x1.40mm_HandSolder; LCSC C17024
C6: 100nF; R_0805_2012Metric_Pad1.20x1.40mm_HandSolder; Voltage 6.3V; Tolerance 20%; LCSC C17024
J1, J2, J3, J4, J5, J6: JST_2mm_3; JST_1x03_P2.0mm_Vertical_PTH
J7: Conn_01x02; JST_PH_B2B-PH-K_1x02_P2.00mm_Vertical
J8: Screw_Terminal_01x05; TerminalBlock_RND_205-00048_1x05_P5.00mm_Horizontal
R1, R3, R5, R6, R7, R9, R10: R; R_0805_2012Metric_Pad1.15x1.40mm; LCSC C17414
R2, R4: R; R_0805_2012Metric_Pad1.15x1.40mm; LCSC C17516
R8: R; R_0805_2012Metric_Pad1.15x1.40mm; LCSC C17513
U1: PC817; DIP-4_W7.62mm_LongPads; LCSC C3025068
U2: ESP-01v090; ESP-01

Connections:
+3V3: J7.2, R5.1, R6.1, R7.1, R9.2, U2.3 (CH_PD), U2.7 (VCC)
GND: C1.1, C2.1, C3.1, C4.1, C5.1, C6.2, J1.2, J2.2, J3.2, J4.2, J5.2, J6.2, J7.1, J8.1, J8.2, J8.3, J8.4, J8.5, R2.2, R4.2, U1.2, U1.3, U2.2 (GND)
unnamed: C1.2, J1.3, R1.2, R2.1
unnamed: C2.2, J2.3, R3.2, R4.1
unnamed: C3.2, J3.1, J3.3, R5.2
unnamed: C4.2, J4.1, J4.3, R6.2
unnamed: C5.2, J5.1, J5.3, R7.2
unnamed: C6.1, J6.3, R10.1
unnamed: J1.1, R1.1
unnamed: J2.1, R3.1
unnamed: J6.1, R8.1
unnamed: R8.2, U1.1
unnamed: R9.1, U1.4, U2.6 (GPIO0)
unnamed: R10.2, U2.4 (GPIO2)

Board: 2 copper layers, 26 parts (0 on the bottom side), 14 nets, no tracks yet.

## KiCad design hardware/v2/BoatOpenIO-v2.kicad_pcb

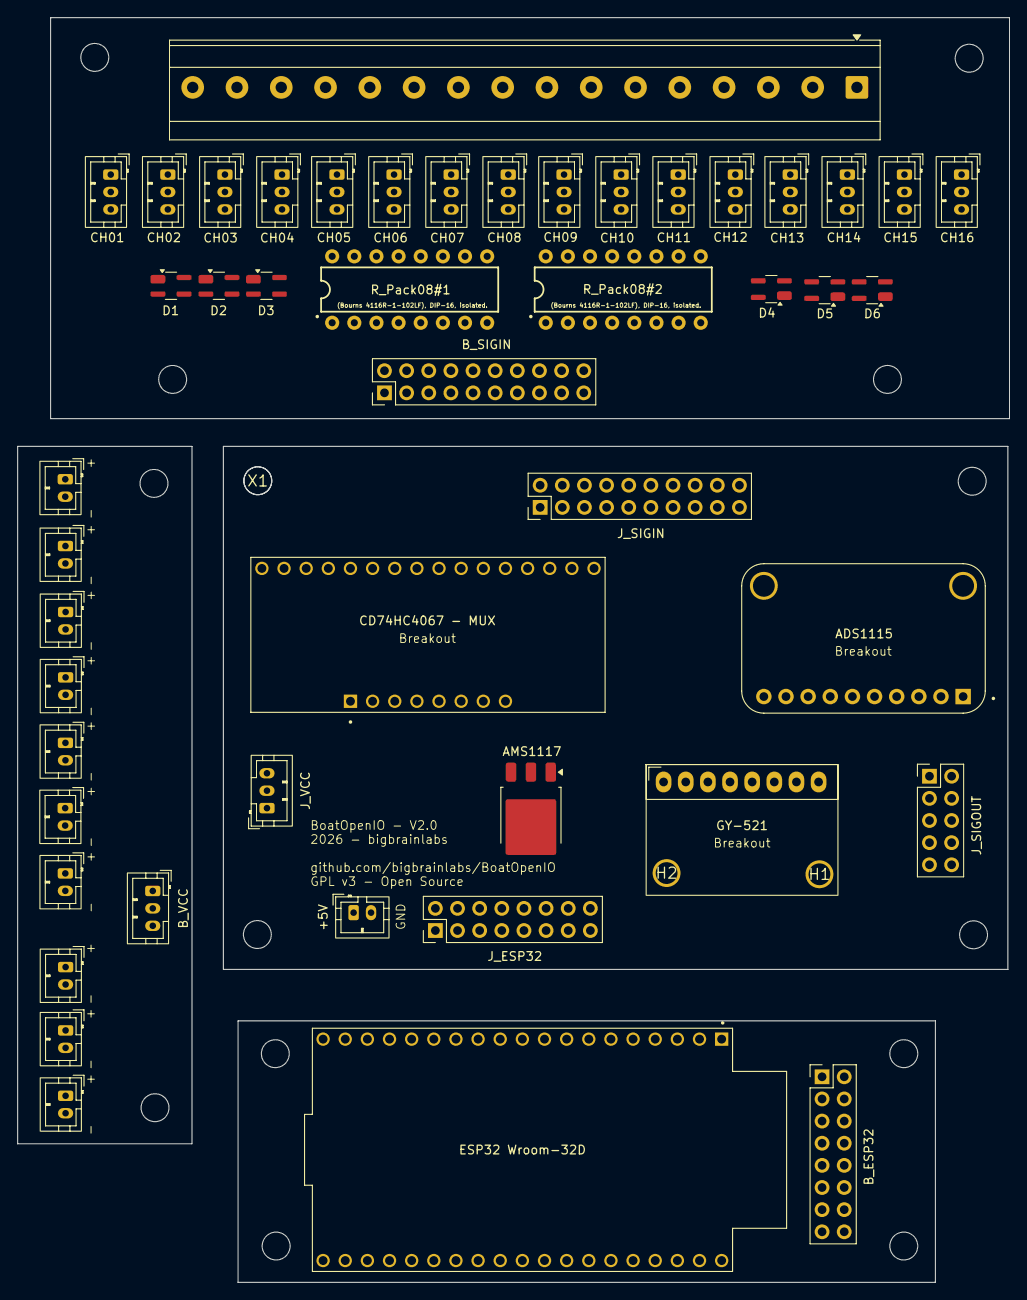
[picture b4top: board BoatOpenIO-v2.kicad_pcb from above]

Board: 2 copper layers, 113.8 x 145.1 mm, 65 parts (0 on the bottom side), 100 nets, no tracks yet.

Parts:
3.3V#1, 3.3V#2, 3.3V#3, 3.3V#4, 3.3V#5, 3.3V#6, 3.3V#7, 5V#1, 5V#2, 5V#3: Conn_01x02; JST_PH_B2B-PH-K_1x02_P2.00mm_Vertical
+5V: Conn_01x02; JST_PH_B2B-PH-K_1x02_P2.00mm_Vertical
ADS1115: ZC261500; MODULE_ZC261500
AMS1117: AMS1117CD-3.3; TO-252-3_TabPin2
B1, B2, B3, B4, B5, B6, B7, B8, B9, B10, B11, B12, B13, B14: MountingHole_3.2mm_M3
B_ESP32: Conn_02x08_Odd_Even; PinHeader_2x08_P2.54mm_Vertical
B_SIGIN: Conn_02x10_Odd_Even; PinHeader_2x10_P2.54mm_Vertical
B_VCC: Conn_01x03_Pin; JST_PH_B3B-PH-K_1x03_P2.00mm_Vertical
CD74HC4067 - MUX: BOB-09056; MODULE_BOB-09056
CH01, CH02, CH03, CH04, CH05, CH06, CH07, CH08, CH09, CH10, CH11, CH12, CH13, CH14, CH15, CH16: Conn_01x03_Pin; JST_PH_B3B-PH-K_1x03_P2.00mm_Vertical
D1, D2, D3, D4, D5, D6: SP0503BAHTG; SOT-143_Handsoldering
ESP32 Wroom-32D: ESP32-WROOM-32D; MODULE_ESP32-DEVKITC
GY-521: MPU6050; MPU6050_Breakout
H1, H2: (no value)
J27: Screw_Terminal_01x16; TerminalBlock_Phoenix_MKDS-3-16-5.08_1x16_P5.08mm_Horizontal
J_ESP32: Conn_02x08_Odd_Even; PinHeader_2x08_P2.54mm_Vertical
J_SIGIN: Conn_02x10_Odd_Even; PinHeader_2x10_P2.54mm_Vertical
J_SIGOUT: Conn_02x05_Odd_Even; PinHeader_2x05_P2.54mm_Vertical
J_VCC: Conn_01x03_Pin; JST_PH_B3B-PH-K_1x03_P2.00mm_Vertical
R_Pack08#1, R_Pack08#2: R_Pack08; DIP-16
X1: (no value)

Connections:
GND: 3.3V#1.2, 3.3V#2.2, 3.3V#3.2, 3.3V#4.2, 3.3V#5.2, 3.3V#6.2, 3.3V#7.2, 5V#1.2, 5V#2.2, 5V#3.2, +5V.2, ADS1115.9 (GND), AMS1117.1 (GND), B_SIGIN.20, B_VCC.3, CD74HC4067 - MUX.JP3-1 (GND), CH01.2, CH02.2, CH03.2, CH04.2, CH05.2, CH06.2, CH07.2, CH08.2, CH09.2, CH10.2, CH11.2, CH12.2, CH13.2, CH14.2, CH15.2, CH16.2, D1.1, D2.1, D3.1, D4.1, D5.1, D6.1, GY-521.7 (GND), J_ESP32.2, J_SIGIN.20, J_SIGOUT.2, J_VCC.3
unnamed: CH16.1, J27.1
unnamed: CH16.3, R_Pack08#2.16 (R1.2)
unnamed: CH15.1, J27.2
unnamed: CH15.3, R_Pack08#2.15 (R2.2)
unnamed: CH14.3, R_Pack08#2.14 (R3.2)
unnamed: CH13.3, R_Pack08#2.13 (R4.2)
unnamed: CH12.3, R_Pack08#2.12 (R5.2)
unnamed: CH11.3, R_Pack08#2.11 (R6.2)
unnamed: CH10.3, R_Pack08#2.10 (R7.2)
unnamed: CH09.3, R_Pack08#2.9 (R8.2)
unnamed: CH08.3, R_Pack08#1.16 (R1.2)
unnamed: CH07.1, J27.10
unnamed: CH07.3, R_Pack08#1.15 (R2.2)
unnamed: CH06.1, J27.11
unnamed: CH06.3, R_Pack08#1.14 (R3.2)
unnamed: CH05.1, J27.12
unnamed: CH05.3, R_Pack08#1.13 (R4.2)
unnamed: CH04.1, J27.13
unnamed: CH04.3, R_Pack08#1.12 (R5.2)
unnamed: CH03.1, J27.14
unnamed: CH03.3, R_Pack08#1.11 (R6.2)
unnamed: CH02.1, J27.15
unnamed: CH02.3, R_Pack08#1.10 (R7.2)
unnamed: CH01.1, J27.16
unnamed: CH01.3, R_Pack08#1.9 (R8.2)
unnamed: 3.3V#1.1, 3.3V#2.1, 3.3V#3.1, 3.3V#4.1, 3.3V#5.1, 3.3V#6.1, 3.3V#7.1, B_VCC.1
unnamed: 5V#1.1, 5V#2.1, 5V#3.1, B_VCC.2
unnamed: CH14.1, J27.3
unnamed: CH13.1, J27.4
unnamed: CH12.1, J27.5
unnamed: CH11.1, J27.6
unnamed: CH10.1, J27.7
unnamed: CH09.1, J27.8
unnamed: CH08.1, J27.9
unnamed: +5V.1, AMS1117.3 (VI), J_VCC.2
unnamed: B_SIGIN.1, D1.4, R_Pack08#2.1 (R1.1)
unnamed: B_SIGIN.2, D1.3, R_Pack08#2.2 (R2.1)
unnamed: B_SIGIN.3, D1.2, R_Pack08#2.3 (R3.1)
unnamed: B_SIGIN.4, D2.4, R_Pack08#2.4 (R4.1)
unnamed: B_SIGIN.5, D3.3, R_Pack08#2.5 (R5.1)
unnamed: B_SIGIN.6, D3.2, R_Pack08#2.6 (R6.1)
unnamed: B_SIGIN.7, D2.3, R_Pack08#2.7 (R7.1)
unnamed: B_SIGIN.8, D2.2, R_Pack08#2.8 (R8.1)
unnamed: B_SIGIN.9, D3.4, R_Pack08#1.1 (R1.1)
unnamed: B_SIGIN.10, D4.3, R_Pack08#1.2 (R2.1)
unnamed: B_SIGIN.11, D4.4, R_Pack08#1.3 (R3.1)
unnamed: B_SIGIN.12, D6.4, R_Pack08#1.4 (R4.1)
unnamed: B_SIGIN.13, D4.2, R_Pack08#1.5 (R5.1)
unnamed: B_SIGIN.14, D5.3, R_Pack08#1.6 (R6.1)
unnamed: B_SIGIN.15, D6.3, R_Pack08#1.7 (R7.1)
unnamed: B_SIGIN.16, D6.2, R_Pack08#1.8 (R8.1)
unnamed: CD74HC4067 - MUX.JP1-16 (C15), J_SIGIN.1
unnamed: CD74HC4067 - MUX.JP1-15 (C14), J_SIGIN.2
unnamed: CD74HC4067 - MUX.JP1-14 (C13), J_SIGIN.3
unnamed: CD74HC4067 - MUX.JP1-13 (C12), J_SIGIN.4
unnamed: CD74HC4067 - MUX.JP1-12 (C11), J_SIGIN.5
unnamed: CD74HC4067 - MUX.JP1-11 (C10), J_SIGIN.6
unnamed: CD74HC4067 - MUX.JP1-10 (C9), J_SIGIN.7
unnamed: CD74HC4067 - MUX.JP1-9 (C8), J_SIGIN.8
unnamed: CD74HC4067 - MUX.JP1-8 (C7), J_SIGIN.9
unnamed: CD74HC4067 - MUX.JP1-7 (C6), J_SIGIN.10
unnamed: CD74HC4067 - MUX.JP1-6 (C5), J_SIGIN.11
unnamed: CD74HC4067 - MUX.JP1-5 (C4), J_SIGIN.12
unnamed: CD74HC4067 - MUX.JP1-4 (C3), J_SIGIN.13
unnamed: CD74HC4067 - MUX.JP1-3 (C2), J_SIGIN.14
unnamed: CD74HC4067 - MUX.JP1-2 (C1), J_SIGIN.15
unnamed: CD74HC4067 - MUX.JP1-1 (C0), J_SIGIN.16
unnamed: ADS1115.10 (VDD), AMS1117.2 (VO), CD74HC4067 - MUX.JP3-2 (VCC), GY-521.8 (VCC), J_ESP32.1, J_SIGOUT.1, J_VCC.1
unnamed: B_ESP32.1, ESP32 Wroom-32D.1 (3V3)
unnamed: B_ESP32.2, ESP32 Wroom-32D.38 (GND3)
unnamed: B_ESP32.3, ESP32 Wroom-32D.36 (IO22)
unnamed: B_ESP32.4, ESP32 Wroom-32D.33 (IO21)
unnamed: B_ESP32.5, ESP32 Wroom-32D.26 (IO4)
unnamed: B_ESP32.6, ESP32 Wroom-32D.29 (IO5)
unnamed: B_ESP32.7, ESP32 Wroom-32D.15 (IO13)
unnamed: B_ESP32.8, ESP32 Wroom-32D.27 (IO16)
unnamed: B_ESP32.9, ESP32 Wroom-32D.28 (IO17)
unnamed: B_ESP32.10, ESP32 Wroom-32D.9 (IO25)
unnamed: B_ESP32.11, ESP32 Wroom-32D.30 (IO18)
unnamed: B_ESP32.12, ESP32 Wroom-32D.10 (IO26)
unnamed: B_ESP32.13, ESP32 Wroom-32D.31 (IO19)
unnamed: B_ESP32.14, ESP32 Wroom-32D.11 (IO27)
unnamed: B_ESP32.15, ESP32 Wroom-32D.37 (IO23)
unnamed: B_ESP32.16, ESP32 Wroom-32D.12 (IO14)
unnamed: ADS1115.8 (SCL), GY-521.6 (SCL), J_ESP32.3
unnamed: ADS1115.7 (SDA), GY-521.5 (SDA), J_ESP32.4
unnamed: J_ESP32.5, J_SIGOUT.3
unnamed: J_ESP32.6, J_SIGOUT.4
unnamed: J_ESP32.7, J_SIGOUT.5
unnamed: J_ESP32.8, J_SIGOUT.6
unnamed: J_ESP32.9, J_SIGOUT.7
unnamed: CD74HC4067 - MUX.JP3-7 (S3), J_ESP32.10
unnamed: J_ESP32.11, J_SIGOUT.8
unnamed: CD74HC4067 - MUX.JP3-6 (S2), J_ESP32.12
unnamed: J_ESP32.13, J_SIGOUT.9
unnamed: CD74HC4067 - MUX.JP3-5 (S1), J_ESP32.14
unnamed: J_ESP32.15, J_SIGOUT.10
unnamed: CD74HC4067 - MUX.JP3-4 (S0), J_ESP32.16
unnamed: ADS1115.4 (A0), CD74HC4067 - MUX.JP3-8 (COM)

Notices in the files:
hardware/boardopenio/boardopenio.kicad_pcb:
GPL v3 - Open Source
